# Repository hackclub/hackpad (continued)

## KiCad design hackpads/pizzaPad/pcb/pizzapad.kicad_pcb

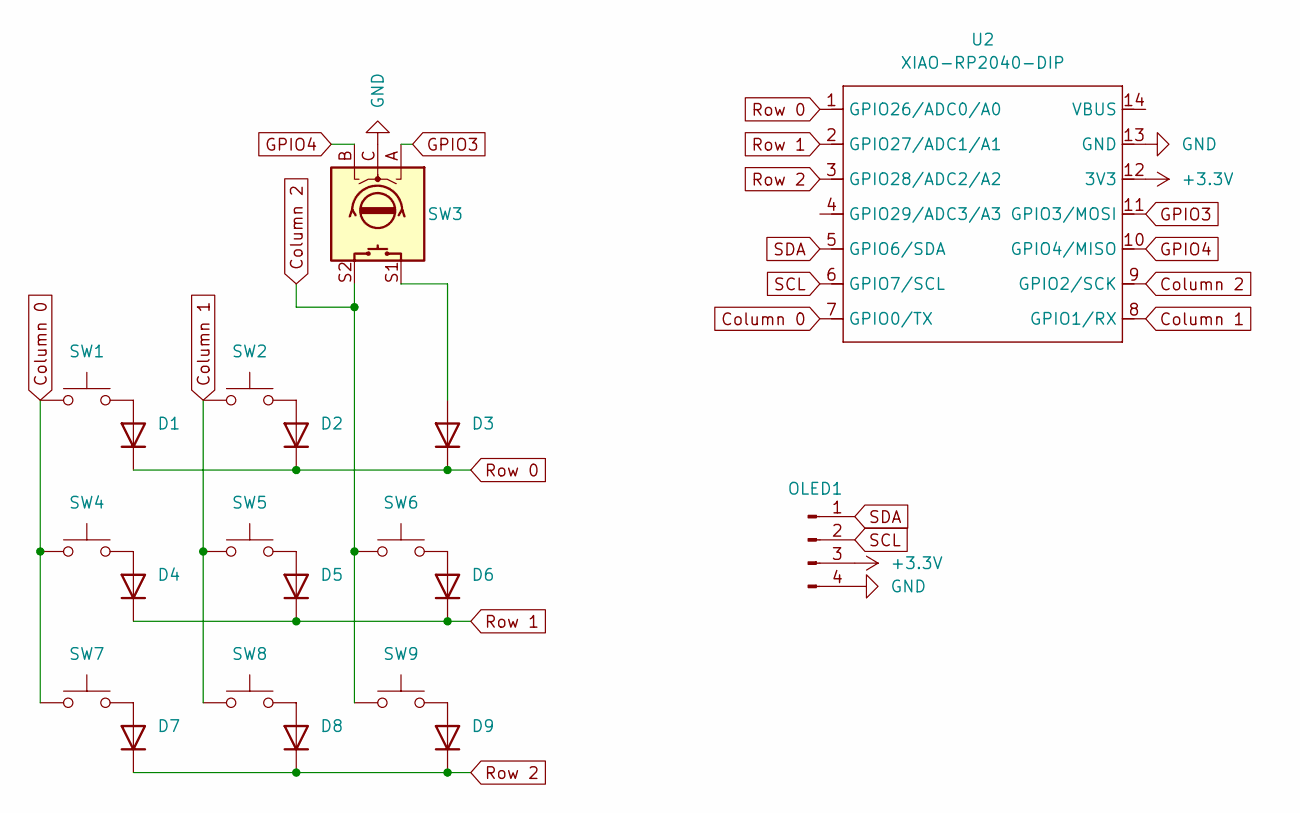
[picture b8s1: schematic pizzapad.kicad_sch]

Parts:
D1, D2, D3, D4, D5, D6, D7, D8, D9: D; D_DO-35_SOD27_P7.62mm_Horizontal
OLED1: Conn_01x04_Pin; MODULE_DM-OLED096-636
SW1, SW2, SW4, SW5, SW6, SW7, SW8, SW9: SW_Push; SW_Cherry_MX_1.00u_PCB
SW3: RotaryEncoder_Switch; RotaryEncoder_Alps_EC11E-Switch_Vertical_H20mm_CircularMoun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
U2: XIAO-RP2040-DIP

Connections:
+3.3V: OLED1.3, U2.12 (3V3); also elsewhere on the board
Column 0: SW1.1, SW4.1, SW7.1, U2.7 (GPIO0/TX); also elsewhere on the board
Column 1: SW2.1, SW5.1, SW8.1, U2.8 (GPIO1/RX); also elsewhere on the board
Column 2: SW3.S2, SW6.1, SW9.1, U2.9 (GPIO2/SCK); also elsewhere on the board
GND: OLED1.4, SW3.C, U2.13 (GND); also elsewhere on the board
GPIO3: SW3.A, U2.11 (GPIO3/MOSI); also elsewhere on the board
GPIO4: SW3.B, U2.10 (GPIO4/MISO); also elsewhere on the board
unnamed: D1.2 (A), SW1.2
unnamed: D2.2 (A), SW2.2
unnamed: D3.2 (A), SW3.S1
unnamed: D4.2 (A), SW4.2
unnamed: D5.2 (A), SW5.2
unnamed: D6.2 (A), SW6.2
unnamed: D7.2 (A), SW7.2
unnamed: D8.2 (A), SW8.2
unnamed: D9.2 (A), SW9.2
Row 0: D1.1 (K), D2.1 (K), D3.1 (K), U2.1 (GPIO26/ADC0/A0); also elsewhere on the board
Row 1: D4.1 (K), D5.1 (K), D6.1 (K), U2.2 (GPIO27/ADC1/A1); also elsewhere on the board
Row 2: D7.1 (K), D8.1 (K), D9.1 (K), U2.3 (GPIO28/ADC2/A2); also elsewhere on the board
SCL: OLED1.2, U2.6 (GPIO7/SCL); also elsewhere on the board
SDA: OLED1.1, U2.5 (GPIO6/SDA); also elsewhere on the board

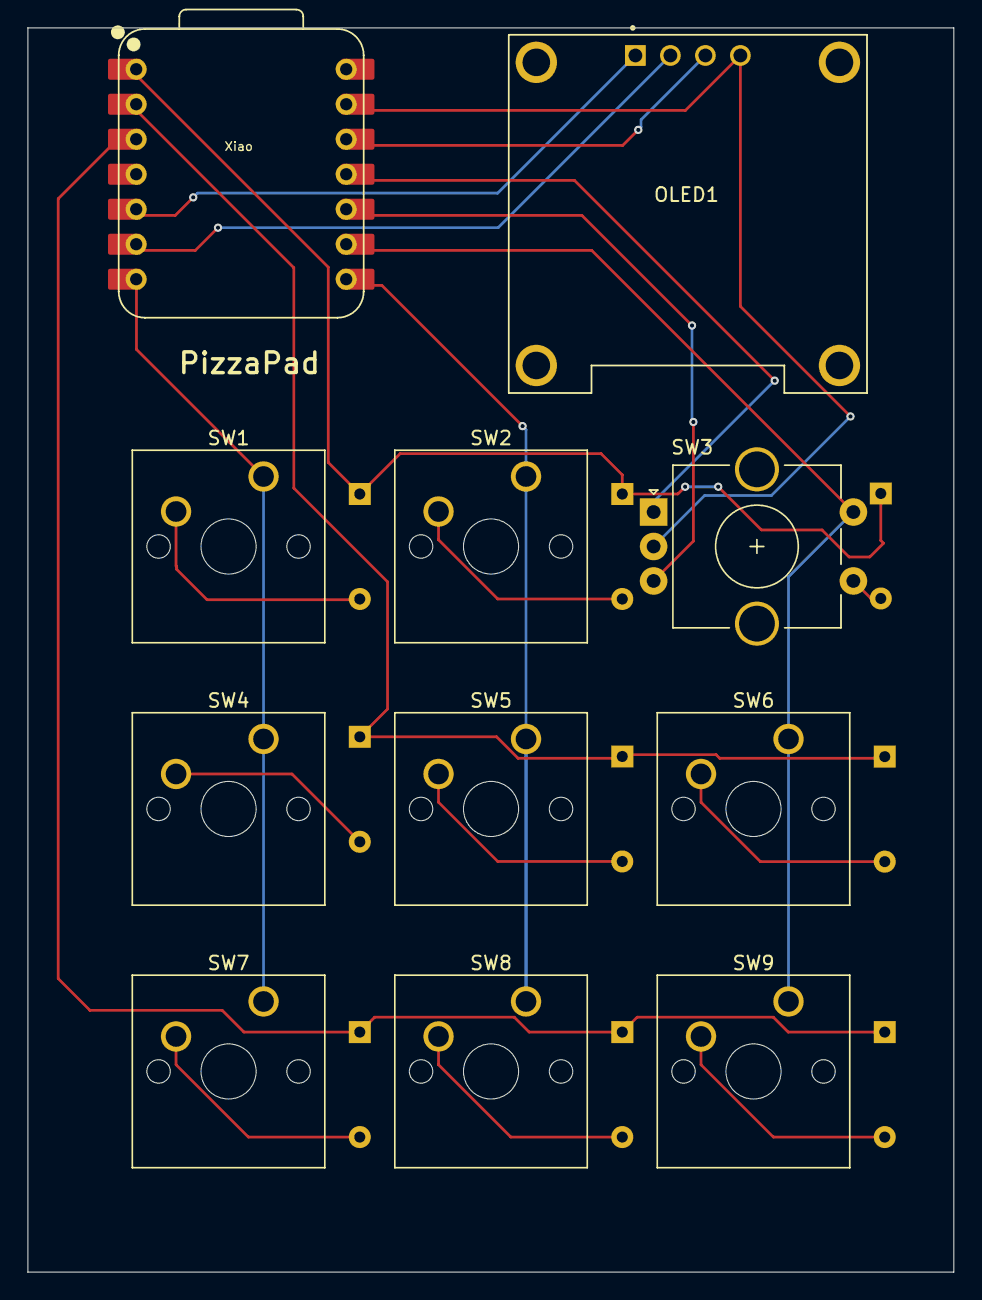
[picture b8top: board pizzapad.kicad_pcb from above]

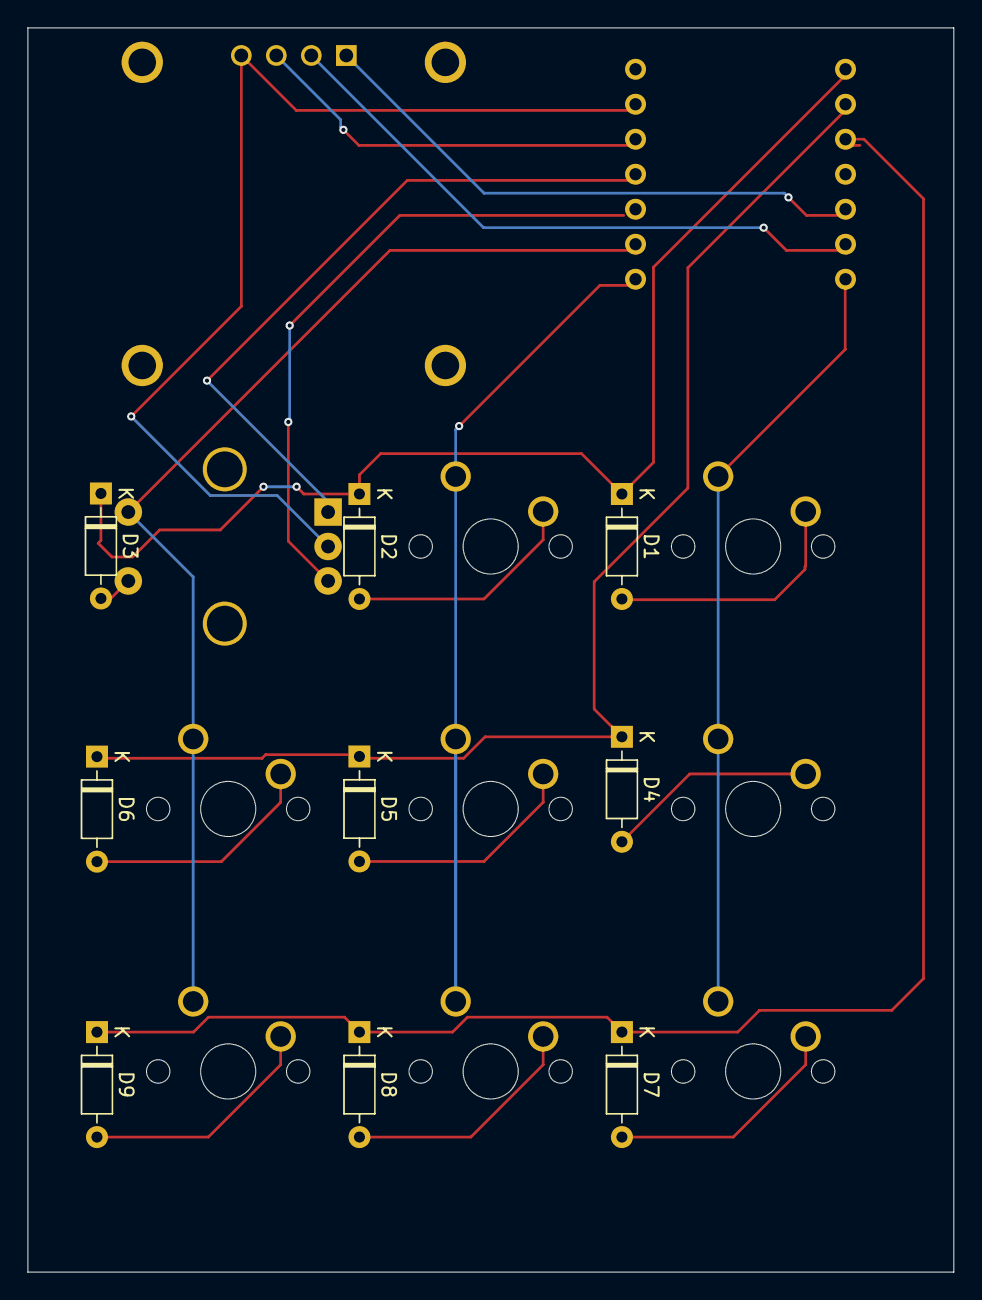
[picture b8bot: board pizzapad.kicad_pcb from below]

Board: 2 copper layers, 67.2 x 90.3 mm, 20 parts (9 on the bottom side), 21 nets.

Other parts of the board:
Xiao: XIAO-RP2040-DIP

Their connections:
+3.3V: Xiao.12 (3V3); also elsewhere on the board
Column 0: Xiao.7 (GPIO0/TX); also elsewhere on the board
Column 1: Xiao.8 (GPIO1/RX); also elsewhere on the board
Column 2: Xiao.9 (GPIO2/SCK); also elsewhere on the board
GND: Xiao.13 (GND); also elsewhere on the board
GPIO3: Xiao.11 (GPIO3/MOSI); also elsewhere on the board
GPIO4: Xiao.10 (GPIO4/MISO); also elsewhere on the board
Row 0: Xiao.1 (GPIO26/ADC0/A0); also elsewhere on the board
Row 1: Xiao.2 (GPIO27/ADC1/A1); also elsewhere on the board
Row 2: Xiao.3 (GPIO28/ADC2/A2); also elsewhere on the board
SCL: Xiao.6 (GPIO7/SCL); also elsewhere on the board
SDA: Xiao.5 (GPIO6/SDA); also elsewhere on the board
